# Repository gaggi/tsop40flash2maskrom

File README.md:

# tsop40flash2maskrom
Adapter for soldering 5v TSOP40 Chips to SNES Carts, with the option to solder a standard TSOP40 chip on the top <b>OR</b> an TSOP40 chip in reverse pinout on the bottom.

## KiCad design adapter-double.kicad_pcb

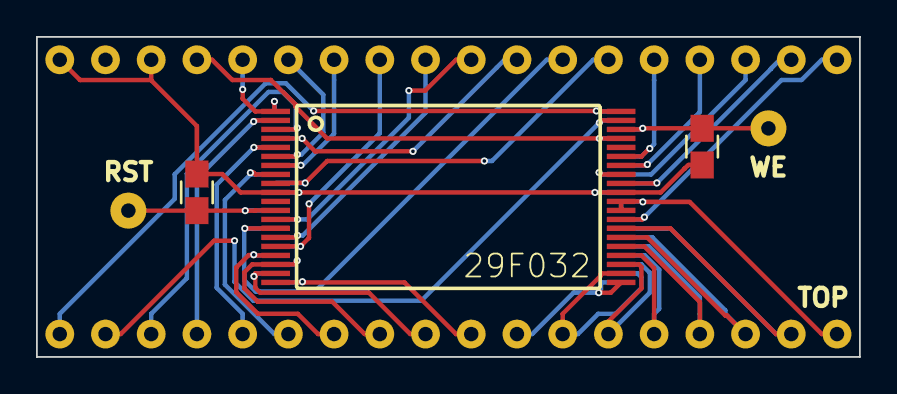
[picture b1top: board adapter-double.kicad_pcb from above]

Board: 2 copper layers, 45.7 x 17.8 mm, 7 parts (1 on the bottom side), 36 nets.

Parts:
PAD_RST: SolderWirePad_single_0-8mmDrill
PAD_WE: SolderWirePad_single_0-8mmDrill
R1, R2: R; R_0805_HandSoldering
U1: SNES_Mask_ROM; DIP-40_W15.24mm
U2: 29F032; TSOP40
U3: 29F032; TSOP40-REVERSE

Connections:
/A0: U1.14, U2.24, U3.24
/A1: U1.13, U2.23, U3.23
/A2: U1.12, U2.22, U3.22
/A3: U1.11, U2.21, U3.21
/A4: U1.10, U2.20, U3.20
/A5: U1.9, U2.19, U3.19
/A6: U1.8, U2.18, U3.18
/A7: U1.7, U2.17, U3.17
/A8: U1.29, U2.16, U3.16
/A9: U1.28, U2.15, U3.15
/A10: U1.25, U2.14, U3.14
/A11: U1.27, U2.13, U3.13
/A12: U1.6, U2.8, U3.8
/A13: U1.30, U2.7, U3.7
/A14: U1.31, U2.6, U3.6
/A15: U1.5, U2.5, U3.5
/A16: U1.26, U2.4, U3.4
/A17: U1.3, U2.3, U3.3
/A18: U1.4, U2.2, U3.2
/A19: U1.32, U2.1, U3.1
/A20: U1.1, U2.40, U3.40
/A21: U1.2, U2.39, U3.39
/CE: U1.24, U2.9, U3.9
/D0: U1.15, U2.25, U3.25
/D1: U1.16, U2.26, U3.26
/D2: U1.17, U2.27, U3.27
/D3: U1.19, U2.28, U3.28
/D4: U1.20, U2.32, U3.32
/D5: U1.21, U2.33, U3.33
/D6: U1.22, U2.34, U3.34
/D7: U1.23, U2.35, U3.35
/OE: U1.33, U2.37, U3.37
/RST: PAD_RST.1, R2.2, U2.12, U3.12
/WE: PAD_WE.1, R1.2, U2.38, U3.38
GND: U1.18, U2.29, U2.30, U3.29, U3.30
VCC: R1.1, R2.1, U1.34, U1.36, U2.10, U2.31, U3.10, U3.31

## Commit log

2016-08-10 :confetti_ball: Added .gitattributes & .gitignore files
2016-08-10 Inital Release
